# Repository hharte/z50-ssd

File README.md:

# Z50-SSD: Solid-State Disk Controller for the Z50Bus

## Introduction

This project implements a solid-state disk controller for the [LiNC Z50Bus](http://linc.no/products/z50bus/).  It is based on the [z80_ssd](https://github.com/hharte/z80_ssd) and utilizes the same firmware.  The only difference between the z80_ssd and the Z50-SSD is the physical board layout and connector.

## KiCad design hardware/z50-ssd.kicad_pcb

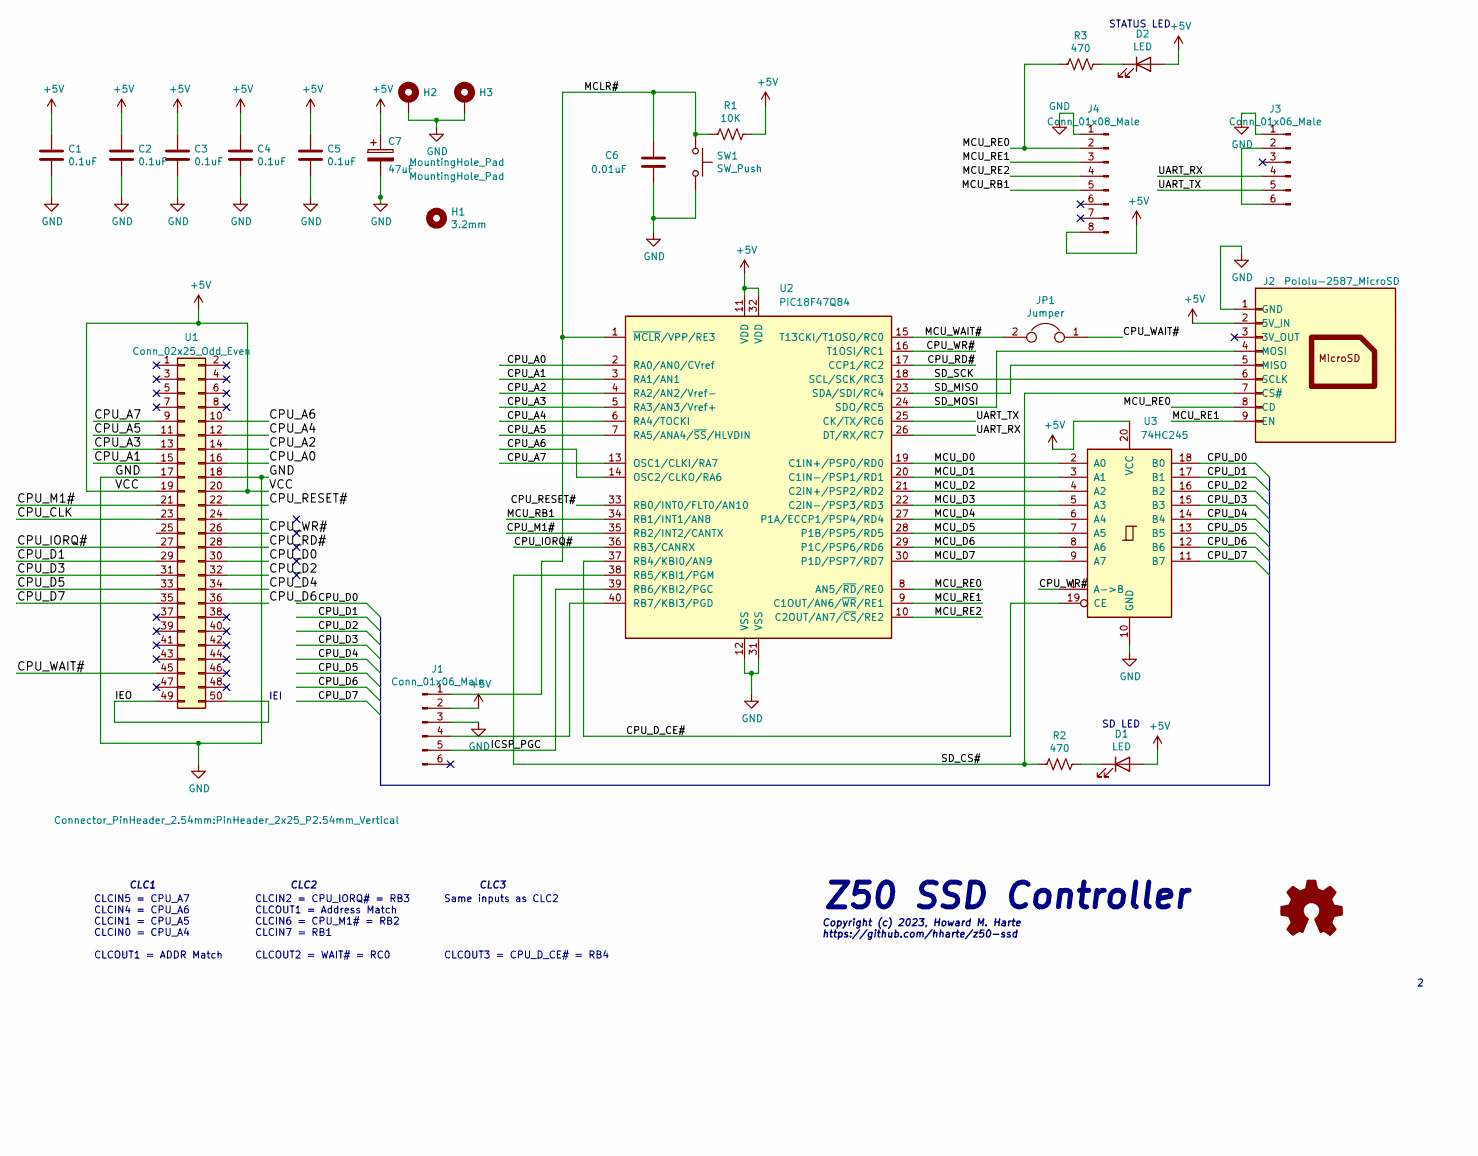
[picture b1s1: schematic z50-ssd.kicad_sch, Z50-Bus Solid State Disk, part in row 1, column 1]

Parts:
C1, C2, C3, C4, C5: 0.1uF; C_Disc_D4.3mm_W1.9mm_P5.00mm
C6: 0.01uF; C_Disc_D4.3mm_W1.9mm_P5.00mm
C7: 47uF; CP_Radial_D6.3mm_P2.50mm
D1, D2: LED; LED_D5.0mm
H1: 3.2mm; MountingHole_3.2mm_M3_DIN965
H2, H3: MountingHole_Pad; MountingHole_2.2mm_M2_Pad
J1, J3: Conn_01x06_Male; PinHeader_1x06_P2.54mm_Horizontal
J2: Pololu-2587_MicroSD; PinHeader_1x09_P2.54mm_Vertical
J4: Conn_01x08_Male; PinHeader_1x08_P2.54mm_Vertical
JP1: Jumper; PinHeader_1x02_P2.54mm_Vertical
LOGO1: Logo_Open_Hardware_Small; OSHW-Logo_5.7x6mm_SilkScreen
R1: 10K; R_Axial_DIN0207_L6.3mm_D2.5mm_P7.62mm_Horizontal
R2, R3: 470; R_Axial_DIN0207_L6.3mm_D2.5mm_P7.62mm_Horizontal
SW1: SW_Push; SW_PUSH_6mm
U1: Conn_02x25_Odd_Even; PinHeader_2x25_P2.54mm_Vertical
U2: PIC18F47Q84; DIP-40_W15.24mm_Socket
U3: 74HC245; DIP-20_W7.62mm_Socket

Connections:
+5V: C1.1, C2.1, C3.1, C4.1, C5.1, C7.1, D1.2 (A), D2.2 (A), J1.2, J2.2 (5V_IN), J4.8, R1.1, U1.19, U1.20, U2.11 (VDD), U2.32 (VDD), U3.20 (VCC)
/CPU_A0: U1.16, U2.2 (RA0/AN0/CVref)
/CPU_A1: U1.15, U2.3 (RA1/AN1)
/CPU_A2: U1.14, U2.4 (RA2/AN2/Vref-)
/CPU_A3: U1.13, U2.5 (RA3/AN3/Vref+)
/CPU_A4: U1.12, U2.6 (RA4/TOCKI)
/CPU_A5: U1.11, U2.7 (RA5/ANA4/~SS/HLVDIN)
/CPU_A6: U1.10, U2.14 (OSC2/CLKO/RA6)
/CPU_A7: U1.9, U2.13 (OSC1/CLKI/RA7)
/CPU_CLK: U1.23
/CPU_D0: U1.30, U3.18 (B0)
/CPU_D1: U1.29, U3.17 (B1)
/CPU_D2: U1.32, U3.16 (B2)
/CPU_D3: U1.31, U3.15 (B3)
/CPU_D4: U1.34, U3.14 (B4)
/CPU_D5: U1.33, U3.13 (B5)
/CPU_D6: U1.36, U3.12 (B6)
/CPU_D7: U1.35, U3.11 (B7)
/CPU_D_CE#: U2.37 (RB4/KBI0/AN9), U3.19 (CE)
/CPU_IORQ#: U1.27, U2.36 (RB3/CANRX)
/CPU_M1#: U1.21, U2.35 (RB2/INT2/CANTX)
/CPU_RD#: U1.28, U2.17 (CCP1/RC2)
/CPU_RESET#: U1.22, U2.33 (RB0/INT0/FLT0/AN10)
/CPU_WAIT#: JP1.1, U1.45
/CPU_WR#: U1.26, U2.16 (T1OSI/RC1), U3.1 (A->B)
/ICSP_PGC: J1.5, U2.39 (RB6/KBI2/PGC)
/IEO: U1.49, U1.50
/MCLR#: C6.1, J1.1, R1.2, SW1.1, U2.1 (~MCLR/VPP/RE3)
/MCU_D0: U2.19 (C1IN+/PSP0/RD0), U3.2 (A0)
/MCU_D1: U2.20 (C1IN-/PSP1/RD1), U3.3 (A1)
/MCU_D2: U2.21 (C2IN+/PSP2/RD2), U3.4 (A2)
/MCU_D3: U2.22 (C2IN-/PSP3/RD3), U3.5 (A3)
/MCU_D4: U2.27 (P1A/ECCP1/PSP4/RD4), U3.6 (A4)
/MCU_D5: U2.28 (P1B/PSP5/RD5), U3.7 (A5)
/MCU_D6: U2.29 (P1C/PSP6/RD6), U3.8 (A6)
/MCU_D7: U2.30 (P1D/PSP7/RD7), U3.9 (A7)
/MCU_RB1: J4.5, U2.34 (RB1/INT1/AN8)
/MCU_RE0: J2.8 (CD), J4.2, R3.2, U2.8 (AN5/~RD/RE0)
/MCU_RE1: J2.9 (EN), J4.3, U2.9 (C1OUT/AN6/~WR/RE1)
/MCU_RE2: J4.4, U2.10 (C2OUT/AN7/~CS/RE2)
/MCU_WAIT#: JP1.2, U2.15 (T13CKI/T1OSO/RC0)
/SD_CS#: J2.7 (CS#), R2.2, U2.38 (RB5/KBI1/PGM)
/SD_MISO: J2.5 (MISO), U2.23 (SDA/SDI/RC4)
/SD_MOSI: J2.4 (MOSI), U2.24 (SDO/RC5)
/SD_SCK: J2.6 (SCLK), U2.18 (SCL/SCK/RC3)
/UART_RX: J3.4, U2.26 (DT/RX/RC7)
/UART_TX: J3.5, U2.25 (CK/TX/RC6)
GND: C1.2, C2.2, C3.2, C4.2, C5.2, C6.2, C7.2, H2.1, H3.1, J1.3, J2.1 (GND), J3.1, J4.1, SW1.2, U1.17, U1.18, U2.12 (VSS), U2.31 (VSS), U3.10 (GND)
unnamed: D1.1 (K), R2.1
unnamed: D2.1 (K), R3.1
unnamed: J1.4, U2.40 (RB7/KBI3/PGD)
unnamed: J3.2, J3.6

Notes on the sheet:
Z50 SSD Controller
1D Coin Controller
(c) 2020, Howard M. Harte - WZ2Q https://github.com/hharte/1dcoinctrl
CLC3
1D Coin Controller - Microcontroller
Copyright (c) 2023, Howard M. Harte https://github.com/hharte/z50-ssd
IEI
STATUS LED
CLC1
SD LED
Same inputs as CLC2 CLCOUT3 = CPU_D_CE# = RB4
2020-06-27
CLCIN2 = CPU_IORQ# = RB3 CLCOUT1 = Address Match CLCIN6 = CPU_M1# = RB2 CLCIN7 = RB1 CLCOUT2 = WAIT# = RC0
CLCIN5 = CPU_A7 CLCIN4 = CPU_A6 CLCIN1 = CPU_A5 CLCIN0 = CPU_A4 CLCOUT1 = ADDR Match
CLC2

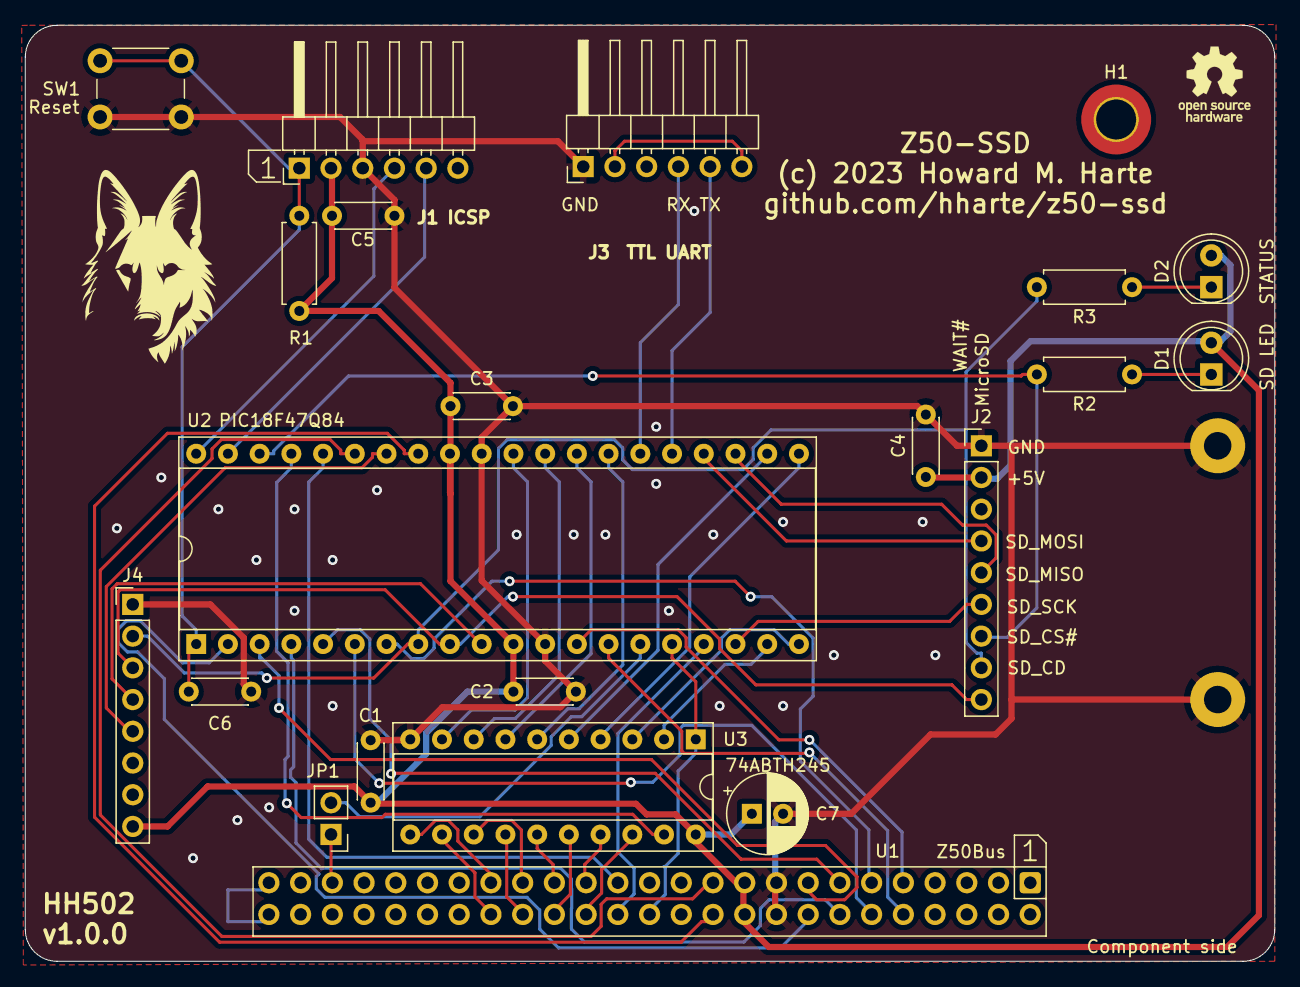
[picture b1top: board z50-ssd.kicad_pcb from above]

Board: 2 copper layers, 100.0 x 74.9 mm, 25 parts (0 on the bottom side), 51 nets.

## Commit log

2023-05-07 Initial version of Z50-SSD, based on z80_ssd.
